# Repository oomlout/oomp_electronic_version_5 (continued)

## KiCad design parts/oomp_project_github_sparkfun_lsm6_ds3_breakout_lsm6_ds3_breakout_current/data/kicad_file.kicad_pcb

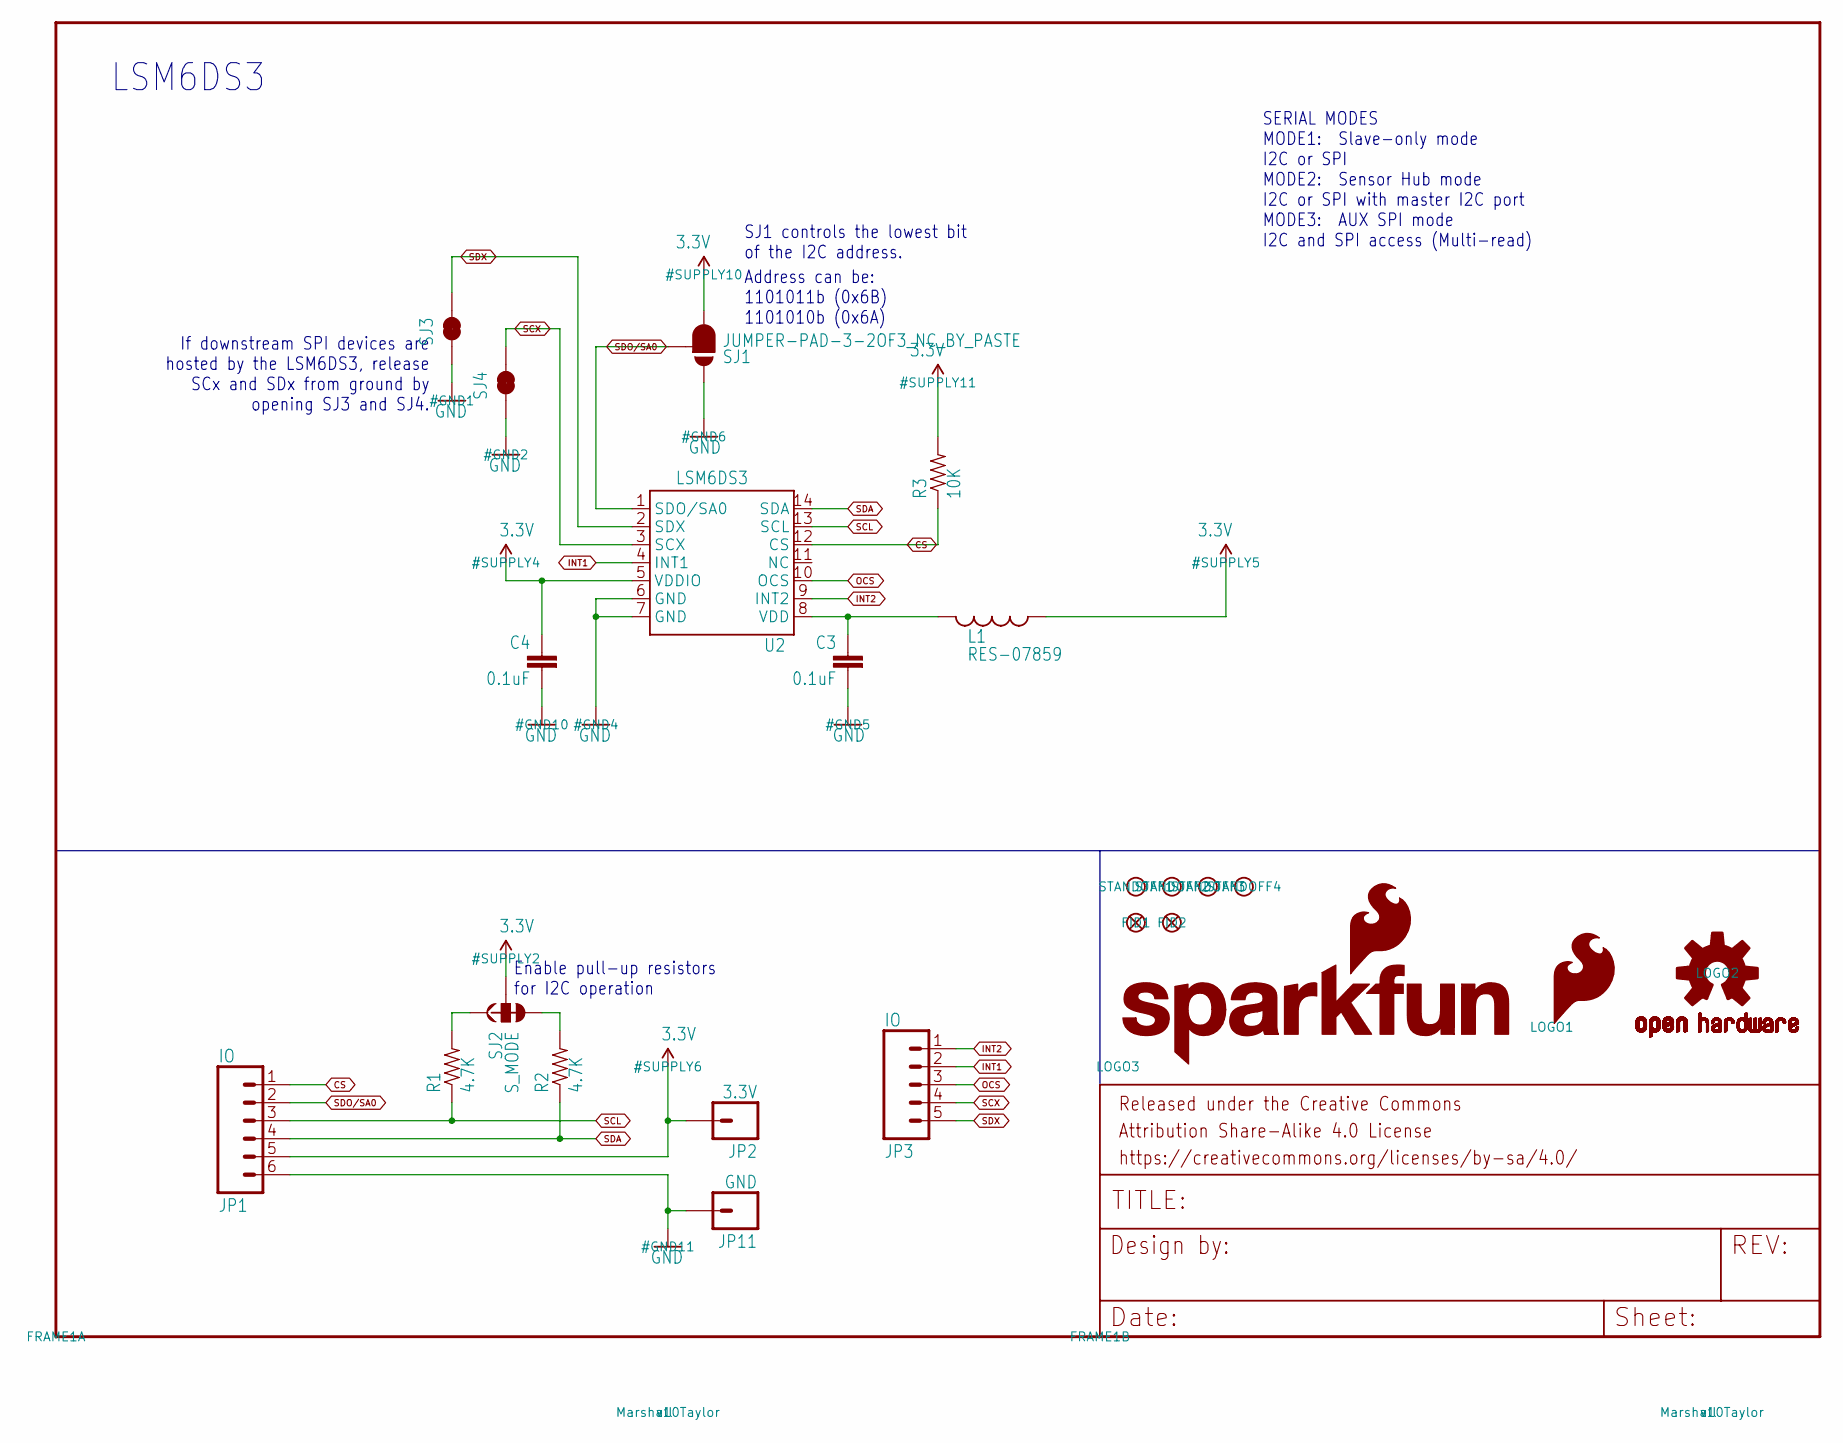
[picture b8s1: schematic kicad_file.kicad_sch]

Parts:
C3, C4: 0.1uF; 0603-CAP
FID1, FID2: FIDUCIAL1X2; FIDUCIAL-1X2
FRAME1: FRAME-LETTER; CREATIVE_COMMONS
JP1: IO; 1X06_NO_SILK_YES_STOP
JP2: 3.3V; 1X01_NO_SILK
JP3: IO; 1X05
JP11: GND; 1X01_NO_SILK
L1: RES-07859; 0603
LOGO1: SFE_LOGO_FLAME.2_INCH; SFE_LOGO_FLAME_.2
LOGO2: OSHW-LOGOS; OSHW-LOGO-S
LOGO3: SFE_LOGO_NAME_FLAME.1_INCH; SFE_LOGO_NAME_FLAME_.1
R1, R2: 4.7K; 0603-RES
R3: 10K; 0603-RES
SJ1: JUMPER-PAD-3-2OF3_NC_BY_PASTE; PAD-JUMPER-3-2OF3_NC_BY_PASTE_YES_SILK_FULL_BOX
SJ2: S_MODE; PAD-JUMPER-3-3OF3_NC_BY_TRACE_YES_SILK_FULL_BOX
SJ3, SJ4: JUMPER-PAD-2-NC_BY_TRACE; PAD-JUMPER-2-NC_BY_TRACE_YES_SILK
STANDOFF1, STANDOFF2, STANDOFF3, STANDOFF4: STAND-OFF
U2: LSM6DS3; LGA14L_DOT_INDICATOR

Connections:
3.3V: C4.1, JP1.5, JP2.1, L1.1, R3.2, SJ1.3, SJ2.2, U2.5 (VDDIO)
CS: JP1.1, R3.1, U2.12 (CS)
GND: C3.2, C4.2, JP1.6, JP11.1, SJ1.1, SJ3.1, SJ4.1, U2.6 (GND), U2.7 (GND)
INT1: JP3.2, U2.4 (INT1)
INT2: JP3.1, U2.9 (INT2)
unnamed: R1.2, SJ2.1
unnamed: R2.2, SJ2.3
OCS: JP3.3, U2.10 (OCS)
SCL: JP1.3, R1.1, U2.13 (SCL)
SCX: JP3.4, SJ4.2, U2.3 (SCX)
SDA: JP1.4, R2.1, U2.14 (SDA)
SDO/SA0: JP1.2, SJ1.2, U2.1 (SDO/SA0)
SDX: JP3.5, SJ3.2, U2.2 (SDX)
VDD: C3.1, L1.2, U2.8 (VDD)

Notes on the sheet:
Address can be: 1101011b (0x6B) 1101010b (0x6A)
SERIAL MODES MODE1: Slave-only mode I2C or SPI MODE2: Sensor Hub mode I2C or SPI with master I2C port MODE3: AUX SPI mode I2C and SPI access (Multi-read)
If downstream SPI devices are hosted by the LSM6DS3, release SCx and SDx from ground by opening SJ3 and SJ4.
SJ1 controls the lowest bit of the I2C address.
Enable pull-up resistors for I2C operation
LSM6DS3

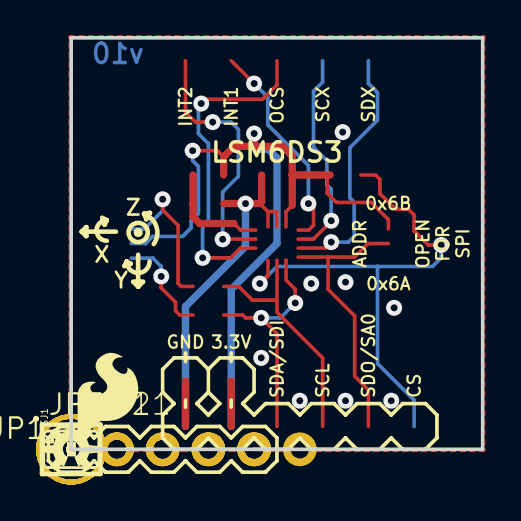
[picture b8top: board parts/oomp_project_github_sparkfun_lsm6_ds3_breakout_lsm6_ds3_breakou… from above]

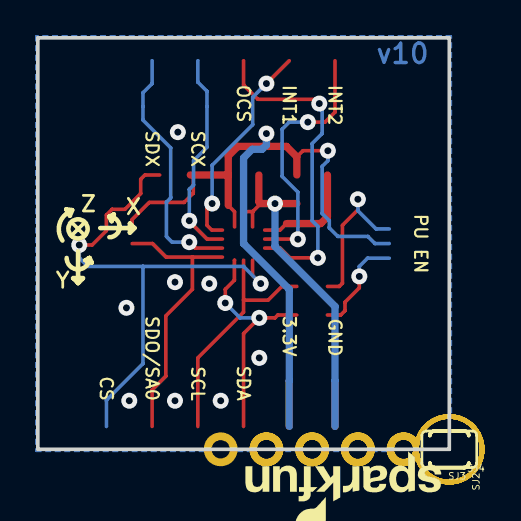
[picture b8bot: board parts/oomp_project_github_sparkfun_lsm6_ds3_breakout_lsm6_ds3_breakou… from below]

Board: 2 copper layers, 22.9 x 22.9 mm, 25 parts (4 on the bottom side), 14 nets.
